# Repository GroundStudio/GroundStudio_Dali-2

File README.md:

GroundStudio Dali-2
====================================

Get it from [ardushop.ro](https://ardushop.ro/ro/home/2657-groundstudio-dali-2.html)

Explore all the GroundStudio products at [GroundStudio.ro](https://groundstudio.ro/)

Description
-------------------
This module can be used to convert the logic signal of a microcontroller from 5V to DALI bus level (9.5 V - 22.5 V) and control lighting systems compatible with the DALI-2 communication protocol.

It can be used together with a development board to control smart lighting systems that use the Dali-2 standard.

Contents
-------------------

* [/Documentation](https://github.com/GroundStudio/GroundStudio_Dali-2/tree/main/Documentation) -- Contains documentation written during creation of this repository, with readme.md index of its own!
* [/Hardware](https://github.com/GroundStudio/GroundStudio_Dali-2/tree/main/Hardware) -- Schematics, layout.

Versions
-------------------
*(Not all tags shown)*
* [V0.0.1] Initial version

License
-------------------

This is released under the [Attribution-ShareAlike 4.0 International (CC BY-SA 4.0)](https://creativecommons.org/licenses/by-sa/4.0/) license. 
**You are welcome to use this for commercial purposes.**

Please consider contributing back to this project or others to help the open-source hardware community continue to thrive and grow! 

Certifications:

[Open Source Hardware Association](https://certification.oshwa.org/ro000022.html)   
   
[
](https://certification.oshwa.org/ro000022.html)

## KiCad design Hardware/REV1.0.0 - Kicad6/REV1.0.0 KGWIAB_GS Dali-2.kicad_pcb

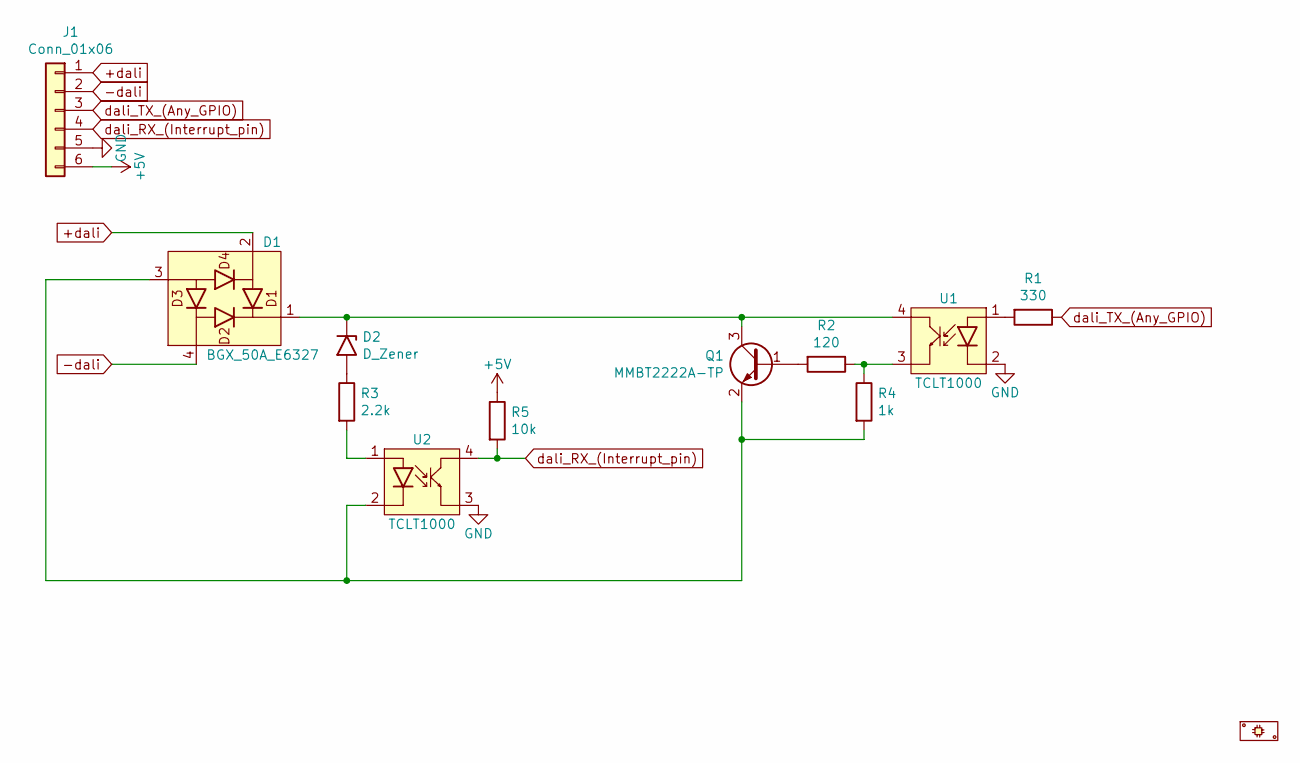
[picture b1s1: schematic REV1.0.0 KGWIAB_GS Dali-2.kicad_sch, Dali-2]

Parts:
D1: BGX_50A_E6327; SOT-143; MPN BGX 50A E6327; LCSC C534261
D2: D_Zener; SOD-523; MPN MM5Z5V1; LCSC C2832572
J1: Conn_01x06; PinHeader_1x06_P2.54mm_Vertical_Male; MPN C37208; LCSC C37208
P1: PCB; MPN KGWIAB_GS_PCB
Q1: MMBT2222A-TP; SOT-23-3; MPN MMBT2222A-TP; LCSC C194252
R1: 330; R_0402_alt; MPN 0402WGF3300TCE; LCSC C25104
R2: 120; R_0402_alt; MPN RC-02W1200FT; LCSC C310190
R3: 2.2k; R_0402_alt; MPN RC-02W2201FT; LCSC C258093
R4: 1k; R_0402_alt; MPN RC-02W1001FT; LCSC C226166
R5: 10k; R_0402_alt; MPN 0402WGJ0103TCE; LCSC C25531
U1, U2: TCLT1000; SOP-4_P2.54_300mil; MPN TCLT1000; LCSC C110644

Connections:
+5V: J1.6, R5.1
+dali: D1.2, J1.1
-dali: D1.4, J1.2
GND: J1.5, U1.2 (K), U2.3 (E)
unnamed: D1.1, D2.1 (K), Q1.3 (C), U1.4 (C)
unnamed: D1.3, Q1.2 (E), R4.2, U2.2 (K)
unnamed: D2.2 (A), R3.1
unnamed: Q1.1 (B), R2.2
unnamed: R1.2, U1.1 (A)
unnamed: R2.1, R4.1, U1.3 (E)
unnamed: R3.2, U2.1 (A)
dali_RX_(Interrupt_pin): J1.4, R5.2, U2.4 (C)
dali_TX_(Any_GPIO): J1.3, R1.1

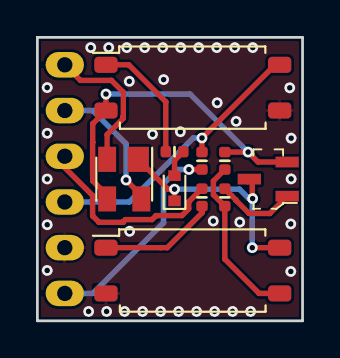
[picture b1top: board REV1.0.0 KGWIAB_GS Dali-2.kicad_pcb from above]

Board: 2 copper layers, 14.7 x 15.7 mm, 11 parts (0 on the bottom side), 13 nets.

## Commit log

2023-10-19 - first commit
2023-10-19 - added kicad6 files, schematical pdf and arduino example code
